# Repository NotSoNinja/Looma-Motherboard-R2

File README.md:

Looma-Motherboard-R2
====================

Revision 2+ of Looma's Motherboard

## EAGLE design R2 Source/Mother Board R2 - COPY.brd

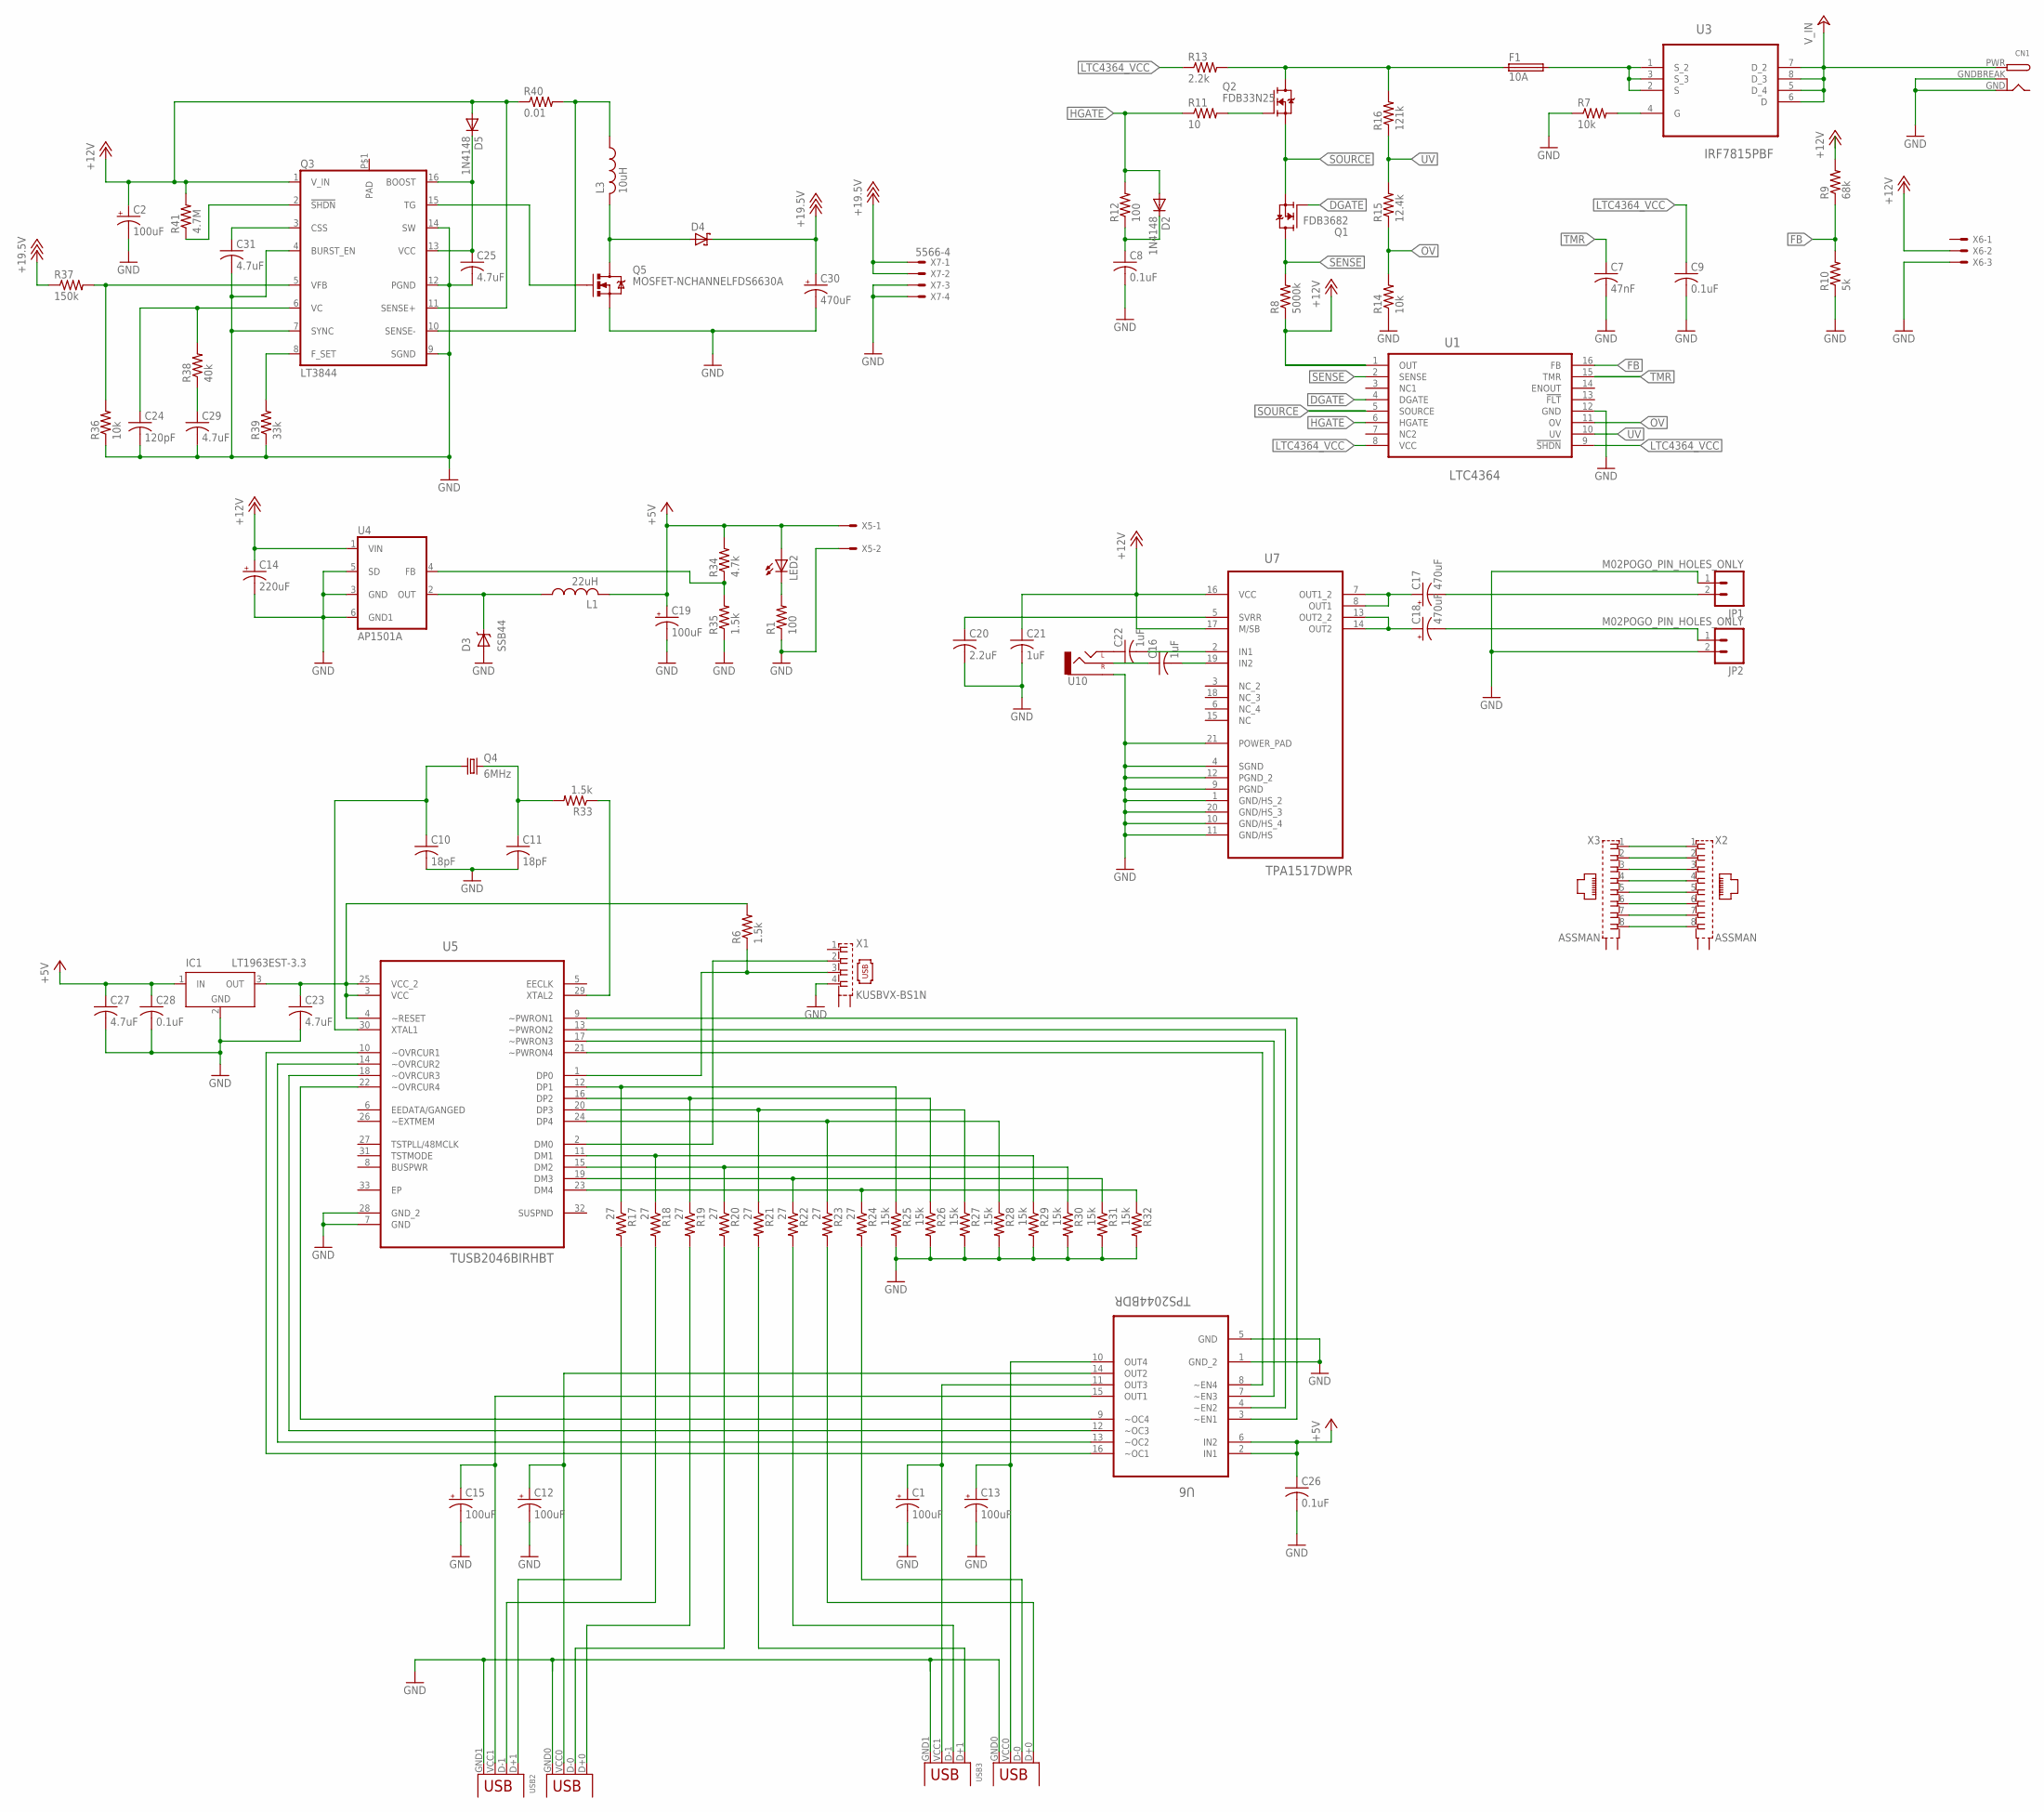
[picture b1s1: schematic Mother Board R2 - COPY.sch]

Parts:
C1, C2, C12, C13, C15, C19: 100uF; PANASONIC_D; MPN 107SML016M
C7: 47nF; C1206; MPN 12061C473KAZ1A
C8, C9, C26, C28: 0.1uF; C0603; MPN 0603YC104MAT2A
C10, C11: 18pF; C0603; MPN 06035A180JAT2A
C14: 220uF; PANASONIC_D; MPN 16SVPF270M
C16, C21, C22: 1uF; C1206; MPN C1206C105K3RACTU
C17, C18, C30: 470uF; PANASONIC_D; MPN 107SML016M
C20: 2.2uF; C1206; MPN 1206YC225KAT2A
C23, C25, C27, C29, C31: 4.7uF; C0805; MPN CGA4J3X7R1C475K125AB
C24: 120pF; C0805; MPN CGA4J3X7R1C475K125AB
CN1: DCBARRELPTH; DCJACK_2MM_PTH
D2, D5: 1N4148; SOD323; MPN 1N4148WS-7-F
D3: SSB44; SMB; MPN SSB44-E3/52T
D4: SCHOTTKY-DIODESMC; DIODE_SMC; MPN B550C-13-F
F1: 10A; MINIFUSE; MPN 01530007Z
IC1: LT1963EST-3.3; SOT223
JP1, JP2: M02POGO_PIN_HOLES_ONLY; 1X02_PP_HOLES_ONLY
L1: 22uH; BOURNSIND; MPN SRR1280-220M
L3: 10uH; BOURNSIND; MPN SRR1280-220M
LED2: LEDCHIPLED_1206; CHIPLED_1206; MPN KP-3216CGCK
Q1: FDB3682; TO263; MPN STB35NF10T4
Q2: FDB33N25; TO263; MPN FDB33N25TM
Q3: LT3844; TSSOP16-TPAD
Q4: 6MHz; HC49UP; MPN ABLSG-6.000MHZ-D-2-Y-T
Q5: MOSFET-NCHANNELFDS6630A; SO08
R1, R12: 100; R1206; MPN MCHP06W2F1000T5E
R6, R33: 1.5k; R1206; MPN MCHP06W2F1501T5E
R7, R14, R36: 10k; R1206; MPN MCHP06W2F1002T5E
R8: 5000k; R1206; MPN CRCW12065M10JNEA
R9: 68k; R1206; MPN CRCW120668K0FKEA
R10: 5k; R1206; MPN ERJ-8ENF5101V
R11: 10; R1206; MPN CRM1206-FX-10R0ELF
R13: 2.2k; R1206; MPN CRCW12062K20FKTA
R15: 12.4k; R1206; MPN CRCW120612K4FKEA
R16: 121k; R1206; MPN CRCW1206121KFKEA
R17, R18, R19, R20, R21, R22, R23, R24: 27; R1206; MPN MCHP06W2F270JT5E
R25, R26, R27, R28, R29, R30, R31, R32: 15k; R1206; MPN MCHP06W2F1502T5E
R34: 4.7k; R1206; MPN MC0125W12061120K
R35: 1.5k; R1206; MPN MC0125W12061120K
R37: 150k; R1206; MPN MCHP06W2F1002T5E
R38: 40k; R1206; MPN MCHP06W2F1002T5E
R39: 33k; R1206; MPN MCHP06W2F1002T5E
R40: 0.01; R1206; MPN MCHP06W2F1002T5E
R41: 4.7M; R1206; MPN MCHP06W2F1002T5E
U1: LTC4364; MSOP-16; MPN LTC4364IS-1#PBF
U3: IRF7815PBF; SOIC127P600X175-8N
U4: AP1501A; TO263-5
U5: TUSB2046BIRHBT; QFN50P500X500X100-33N
U6: TPS2044BDR; SOIC127P600X175-16N
U7: TPA1517DWPR; SOIC127P1030X265-21N; MPN TPA1517DWPR
U10: AUDIO-JACKPTH; AUDIO-JACK; MPN SPC21348
USB2, USB3: DUALUSB; USB-A-DS; MPN 5787617-1
X1: KUSBVX-BS1N; MPN MC32597
X2, X3: ASSMAN
X5: KK-156-2
X6: KK-156-3
X7: 5566-4; MPN 39-29-9042

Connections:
+5V: C19.+, C26.1, C27.1, C28.1, IC1.1 (IN), L1.P$2 (2), LED2.A, R34.2, U6.2 (IN1), U6.6 (IN2), X5.1
+12V: C2.+, C14.+, C21.1, D5.A, Q3.1 (V_IN), Q3.11 (SENSE+), R8.1, R9.2, R40.1, R41.2, U1.1 (OUT), U4.1 (VIN), U7.16 (VCC), U7.17 (M/SB), X6.2
+18V: C30.+, D4.C (A), R37.1, X7.1, X7.2
DGATE: Q1.1 (G), U1.4 (DGATE)
FB: R9.1, R10.2, U1.16 (FB)
GND: C1.-, C2.-, C7.2, C8.2, C9.2, C10.2, C11.2, C12.-, C13.-, C14.-, C15.-, C19.-, C20.2, C21.2, C23.2, C24.2, C25.2, C26.2, C27.2, C28.2, C29.2, C30.-, C31.2, CN1.GND, CN1.GNDBREAK, D3.A, IC1.2 (GND), IC1.4 (GND), JP1.1, JP2.2, Q3.4 (BURST_EN), Q3.7 (SYNC), Q3.9 (SGND), Q3.12 (PGND), Q3.14 (SW), Q5.1 (S), Q5.2 (S), Q5.3 (S), R1.1, R7.1, R10.1, R14.1, R25.2, R26.2, R27.2, R28.2, R29.2, R30.2, R31.2, R32.2, R35.1, R36.1, R39.1, U1.12 (GND), U4.3 (GND), U4.5 (SD), U4.6 (GND1), U5.7 (GND), U5.28 (GND_2), U6.1 (GND_2), U6.5 (GND), U7.1 (GND/HS_2), U7.4 (SGND), U7.9 (PGND), U7.10 (GND/HS_4), U7.11 (GND/HS), U7.12 (PGND_2), U7.20 (GND/HS_3), U7.21 (POWER_PAD), U10.SLEEVE, USB2.GND0 (GND), USB2.GND1, USB3.GND0 (GND), USB3.GND1, X1.4, X5.2, X6.3, X7.3, X7.4
HGATE: D2.A, R11.1, R12.2, U1.6 (HGATE)
LTC4364_VCC: C9.1, R13.1, U1.8 (VCC), U1.9 (!SHDN)
unnamed: F1.P$1 (1), Q2.3 (D), R13.2, R16.2
unnamed: D3.C, L1.P$1 (1), U4.2 (OUT)
unnamed: LED2.C, R1.2
unnamed: U5.2 (DM0), X1.2
unnamed: R6.1, U5.1 (DP0), X1.3
unnamed: C23.1, IC1.3 (OUT), R6.2, U5.3 (VCC), U5.4 (~RESET), U5.25 (VCC_2)
unnamed: R17.1, R25.1, U5.12 (DP1)
unnamed: Q2.1 (G), R11.2
unnamed: R18.1, R29.1, U5.11 (DM1)
unnamed: C8.1, D2.C, R12.1
unnamed: R19.1, R26.1, U5.16 (DP2)
unnamed: F1.P$2 (2), U3.1 (S_2), U3.2 (S), U3.3 (S_3)
unnamed: R20.1, R30.1, U5.15 (DM2)
unnamed: R7.2, U3.4 (G)
unnamed: R21.1, R27.1, U5.20 (DP3)
unnamed: R22.1, R31.1, U5.19 (DM3)
unnamed: R23.1, R28.1, U5.24 (DP4)
unnamed: R24.1, R32.1, U5.23 (DM4)
unnamed: C10.1, Q4.1, U5.30 (XTAL1)
unnamed: C11.1, Q4.2, R33.2
unnamed: R33.1, U5.29 (XTAL2)
unnamed: U5.21 (~PWRON4), U6.8 (~EN4)
unnamed: U5.17 (~PWRON3), U6.7 (~EN3)
unnamed: U5.13 (~PWRON2), U6.4 (~EN2)
unnamed: U5.9 (~PWRON1), U6.3 (~EN1)
unnamed: U5.22 (~OVRCUR4), U6.9 (~OC4)
unnamed: U5.18 (~OVRCUR3), U6.12 (~OC3)
unnamed: U5.14 (~OVRCUR2), U6.13 (~OC2)
unnamed: U5.10 (~OVRCUR1), U6.16 (~OC1)
unnamed: C15.+, U6.15 (OUT1), USB2.VCC1 (VBUS1)
unnamed: C12.+, U6.14 (OUT2), USB2.VCC0 (VBUS)
unnamed: C1.+, U6.11 (OUT3), USB3.VCC1 (VBUS1)
unnamed: C13.+, U6.10 (OUT4), USB3.VCC0 (VBUS)
unnamed: R17.2, USB2.D+1
unnamed: R18.2, USB2.D-1
unnamed: R19.2, USB2.D+0 (D+)
unnamed: R20.2, USB2.D-0 (D-)
unnamed: R21.2, USB3.D+1
unnamed: R22.2, USB3.D-1
unnamed: R23.2, USB3.D+0 (D+)
unnamed: R24.2, USB3.D-0 (D-)
unnamed: C20.1, U7.5 (SVRR)
unnamed: C22.1, U10.TIP (LEFT)
unnamed: C22.2, U7.2 (IN1)
unnamed: C16.1, U10.RING (RIGHT)
unnamed: C16.2, U7.19 (IN2)
unnamed: C17.+, U7.7 (OUT1_2), U7.8 (OUT1)
unnamed: C18.+, U7.13 (OUT2_2), U7.14 (OUT2)
unnamed: C18.-, JP2.1
unnamed: C17.-, JP1.2
unnamed: X2.1, X3.1
unnamed: X2.2, X3.2
unnamed: X2.3, X3.3
unnamed: X2.4, X3.4
unnamed: X2.5, X3.5
unnamed: X2.6, X3.6
unnamed: X2.7, X3.7
unnamed: X2.8, X3.8
unnamed: R34.1, R35.2, U4.4 (FB)
unnamed: Q3.2 (!SHDN), R41.1
unnamed: C31.1, Q3.3 (CSS)
unnamed: C24.1, Q3.6 (VC), R38.2
unnamed: C29.1, R38.1
unnamed: Q3.5 (VFB), R36.2, R37.2
unnamed: Q3.8 (F_SET), R39.2
unnamed: C25.1, D5.C, Q3.13 (VCC), Q3.16 (BOOST)
unnamed: L3.P$1 (1), Q3.10 (SENSE-), R40.2
unnamed: Q3.15 (TG), Q5.4 (G)
unnamed: D4.A (C), L3.P$2 (2), Q5.5 (D), Q5.6 (D), Q5.7 (D), Q5.8 (D)
OV: R14.2, R15.1, U1.11 (OV)
SENSE: Q1.3 (D), R8.2, U1.2 (SENSE)
SOURCE: Q1.2 (S), Q2.2 (S), U1.5 (SOURCE)
TMR: C7.1, U1.15 (TMR)
UV: R15.2, R16.1, U1.10 (UV)
V_IN: CN1.PWR, U3.5 (D_4), U3.6 (D), U3.7 (D_2), U3.8 (D_3)

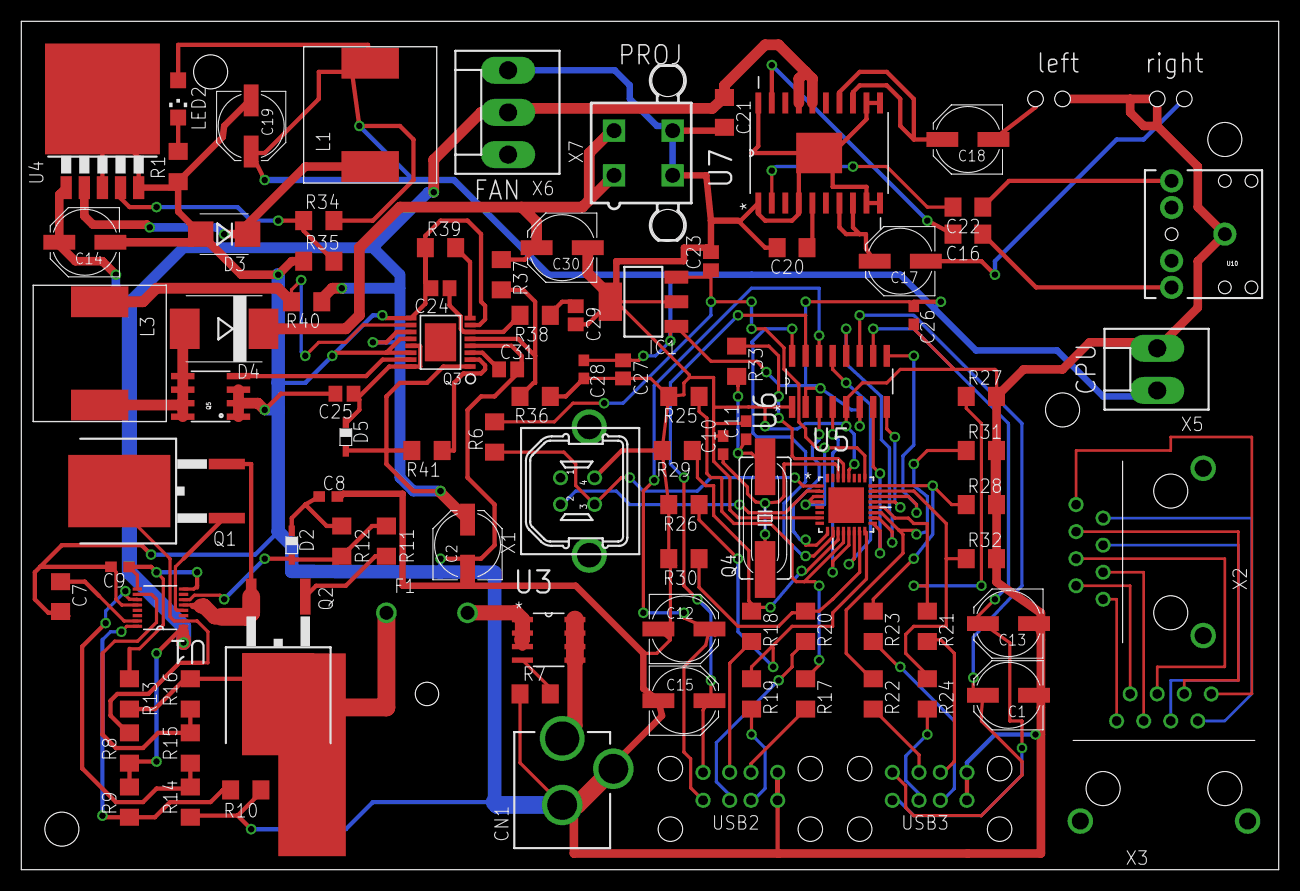
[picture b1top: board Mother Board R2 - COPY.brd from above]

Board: 2 copper layers, 118.1 x 79.7 mm, 96 parts (0 on the bottom side), 83 nets.

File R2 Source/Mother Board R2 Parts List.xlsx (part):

Part | Value | Device | Package | Description | MF | MPN | OC_FARNELL | OC_NEWARK | PACKAGE | PROD_ID | SPICEMODEL | SPICEPREFIX | SPICETYPE | SUPPLIER
R40 | 0.01 | R-US_R1206 | R1206 | RESISTOR, American symbol |  | MCHP06W2F1002T5E |  | 01N7135
R11 | 10 | R-US_R1206 | R1206 | RESISTOR, American symbol |  | CRM1206-FX-10R0ELF |  | 17T4257
R17 | 27 | R-US_R1206 | R1206 | RESISTOR, American symbol |  | MCHP06W2F270JT5E |  | 01N7163
R18 | 27 | R-US_R1206 | R1206 | RESISTOR, American symbol |  | MCHP06W2F270JT5E |  | 01N7163
R19 | 27 | R-US_R1206 | R1206 | RESISTOR, American symbol |  | MCHP06W2F270JT5E |  | 01N7163
R20 | 27 | R-US_R1206 | R1206 | RESISTOR, American symbol |  | MCHP06W2F270JT5E |  | 01N7163
R21 | 27 | R-US_R1206 | R1206 | RESISTOR, American symbol |  | MCHP06W2F270JT5E |  | 01N7163
R22 | 27 | R-US_R1206 | R1206 | RESISTOR, American symbol |  | MCHP06W2F270JT5E |  | 01N7163
R23 | 27 | R-US_R1206 | R1206 | RESISTOR, American symbol |  | MCHP06W2F270JT5E |  | 01N7163
R24 | 27 | R-US_R1206 | R1206 | RESISTOR, American symbol |  | MCHP06W2F270JT5E |  | 01N7163
R1 | 100 | R-US_R1206 | R1206 | RESISTOR, American symbol |  | MCHP06W2F1000T5E |  | 01N7133
R12 | 100 | R-US_R1206 | R1206 | RESISTOR, American symbol |  | MCHP06W2F1000T5E |  | 01N7133
C8 | 0.1uF | C-USC0603 | C0603 | CAPACITOR, American symbol |  | 0603YC104MAT2A |  | 96M1177
C9 | 0.1uF | C-USC0603 | C0603 | CAPACITOR, American symbol |  | 0603YC104MAT2A |  | 96M1177
C26 | 0.1uF | C-USC0603 | C0603 | CAPACITOR, American symbol |  | 0603YC104MAT2A |  | 96M1177
C28 | 0.1uF | C-USC0603 | C0603 | CAPACITOR, American symbol |  | 0603YC104MAT2A |  | 96M1177
R6 | 1.5k | R-US_R1206 | R1206 | RESISTOR, American symbol |  | MCHP06W2F1501T5E |  | 01N7147
R33 | 1.5k | R-US_R1206 | R1206 | RESISTOR, American symbol |  | MCHP06W2F1501T5E |  | 01N7147
R35 | 1.5k | R-US_R1206 | R1206 | RESISTOR, American symbol |  | MCHP06W2F1501T5E |  | 01N7147
C1 | 100uF | CPOL-USD | PANASONIC_D | POLARIZED CAPACITOR, American symbol |  | 107SML016M |  | 99M1145
C2 | 100uF | CPOL-USD | PANASONIC_D | POLARIZED CAPACITOR, American symbol |  | 107SML016M |  | 99M1145
C12 | 100uF | CPOL-USD | PANASONIC_D | POLARIZED CAPACITOR, American symbol |  | 107SML016M |  | 99M1145
C13 | 100uF | CPOL-USD | PANASONIC_D | POLARIZED CAPACITOR, American symbol |  | 107SML016M |  | 99M1145
C15 | 100uF | CPOL-USD | PANASONIC_D | POLARIZED CAPACITOR, American symbol |  | 107SML016M |  | 99M1145
C19 | 100uF | CPOL-USD | PANASONIC_D | POLARIZED CAPACITOR, American symbol |  | 107SML016M |  | 99M1145
F1 | 10A | MINIFUSE | MINIFUSE |  | LITTELFUSE | 01530007Z |  | 67K1420
R7 | 10k | R-US_R1206 | R1206 | RESISTOR, American symbol |  | MCHP06W2F1002T5E |  | 01N7135
R14 | 10k | R-US_R1206 | R1206 | RESISTOR, American symbol |  | MCHP06W2F1002T5E |  | 01N7135
R36 | 10k | R-US_R1206 | R1206 | RESISTOR, American symbol |  | MCHP06W2F1002T5E |  | 01N7135
L3 | 10uH | L-US | BOURNSIND | INDUCTOR, American symbol |  | SRR1280-220M |  | 07W8494
R15 | 12k | R-US_R1206 | R1206 | RESISTOR, American symbol | VISHAY/DALE | CRCW120612K4FKEA |  | 53K1950
C24 | 120pF | C-USC0805 | C0805 | CAPACITOR, American symbol |  | CGA4J3X7R1C475K125AB |  | 04X3165
R16 | 121k | R-US_R1206 | R1206 | RESISTOR, American symbol | VISHAY/DALE | CRCW1206121KFKEA |  | 53K1959
R37 | 150k | R-US_R1206 | R1206 | RESISTOR, American symbol |  | MCHP06W2F1002T5E |  | 01N7135
R25 | 15k | R-US_R1206 | R1206 | RESISTOR, American symbol |  | MCHP06W2F1502T5E |  | 01N7148
R26 | 15k | R-US_R1206 | R1206 | RESISTOR, American symbol |  | MCHP06W2F1502T5E |  | 01N7148
R27 | 15k | R-US_R1206 | R1206 | RESISTOR, American symbol |  | MCHP06W2F1502T5E |  | 01N7148
R28 | 15k | R-US_R1206 | R1206 | RESISTOR, American symbol |  | MCHP06W2F1502T5E |  | 01N7148
R29 | 15k | R-US_R1206 | R1206 | RESISTOR, American symbol |  | MCHP06W2F1502T5E |  | 01N7148
R30 | 15k | R-US_R1206 | R1206 | RESISTOR, American symbol |  | MCHP06W2F1502T5E |  | 01N7148
R31 | 15k | R-US_R1206 | R1206 | RESISTOR, American symbol |  | MCHP06W2F1502T5E |  | 01N7148
R32 | 15k | R-US_R1206 | R1206 | RESISTOR, American symbol |  | MCHP06W2F1502T5E |  | 01N7148
C10 | 18pF | C-USC0603 | C0603 | CAPACITOR, American symbol | AVX CORPORATION | 06035A180JAT2A |  | 17C6481
C11 | 18pF | C-USC0603 | C0603 | CAPACITOR, American symbol | AVX CORPORATION | 06035A180JAT2A |  | 17C6481
D2 | 1N4148 | 1N4148 | SOD323 |  |  | 1N4148WS-7-F |  | 12T2305
D5 | 1N4148 | 1N4148 | SOD323 |  |  | 1N4148WS-7-F |  | 12T2305
C21 | 1uF | C-USC1206 | C1206 | CAPACITOR, American symbol |  | C1206C105K3RACTU |  | 03M7475
R13 | 2.2k | R-US_R1206 | R1206 | RESISTOR, American symbol | VISHAY/DALE | CRCW12062K20FKTA |  | 07J5728
C20 | 2.2uF | C-USC1206 | C1206 | CAPACITOR, American symbol |  | 1206YC225KAT2A |  | 88W4192
C14 | 220uF | CPOL-USD | PANASONIC_D | POLARIZED CAPACITOR, American symbol |  | 16SVPF270M |  | 98W0218
L1 | 22uH | L-US | BOURNSIND | INDUCTOR, American symbol |  | SRR1280-220M |  | 07W8494
R39 | 33k | R-US_R1206 | R1206 | RESISTOR, American symbol |  | MCHP06W2F1002T5E |  | 01N7135
R34 | 4.7k | R-US_R1206 | R1206 | RESISTOR, American symbol |  | MCPWR06FTEO4701 |  | 43T5644
R41 | 4.7M | R-US_R1206 | R1206 | RESISTOR, American symbol |  | MCHP06W2F1002T5E |  | 01N7135
C16 | 4.7uF | C-USC1206 | C1206 | CAPACITOR, American symbol |  | C1206C105K3RACTU |  | 03M7475
C22 | 4.7uF | C-USC1206 | C1206 | CAPACITOR, American symbol |  | C1206C105K3RACTU |  | 03M7475
C23 | 4.7uF | C-USC0805 | C0805 | CAPACITOR, American symbol |  | CGA4J3X7R1C475K125AB |  | 04X3165
C25 | 4.7uF | C-USC0805 | C0805 | CAPACITOR, American symbol |  | CGA4J3X7R1C475K125AB |  | 04X3165
C27 | 4.7uF | C-USC0805 | C0805 | CAPACITOR, American symbol |  | CGA4J3X7R1C475K125AB |  | 04X3165
C29 | 4.7uF | C-USC0805 | C0805 | CAPACITOR, American symbol |  | CGA4J3X7R1C475K125AB |  | 04X3165
C31 | 4.7uF | C-USC0805 | C0805 | CAPACITOR, American symbol |  | CGA4J3X7R1C475K125AB |  | 04X3165
R38 | 39.2k | R-US_R1206 | R1206 | RESISTOR, American symbol |  | MCHP06W2F1002T5E |  | 01N7135
C17 | 470uF | CPOL-USD | PANASONIC_D | POLARIZED CAPACITOR, American symbol |  | 107SML016M |  | 99M1145
C18 | 470uF | CPOL-USD | PANASONIC_D | POLARIZED CAPACITOR, American symbol |  | 107SML016M |  | 99M1145
C30 | 470uF | CPOL-USD | PANASONIC_D | POLARIZED CAPACITOR, American symbol |  | 107SML016M |  | 99M1145
C7 | 47nF | C-USC1206 | C1206 | CAPACITOR, American symbol |  | 12061C473KAZ1A |  | 26M5748
R8 | 5.1M | R-US_R1206 | R1206 | RESISTOR, American symbol |  | CRCW12065M10JNEA |  | 59M6999
X7 | 5566-4 | 5566-4 | 5566-4 | Mini FIT connector 4 pol |  |  | unknown | unknown
R10 | 5.1k | R-US_R1206 | R1206 | RESISTOR, American symbol |  | ERJ-8ENF5101V |  | 53W4995
R9 | 68k | R-US_R1206 | R1206 | RESISTOR, American symbol | VISHAY/DALE | CRCW120668K0FKEA |  | 53K2569
Q4 | 6MHz | CRYSTALHC49UP | HC49UP | CRYSTAL |  | ABLSG-6.000MHZ-D-2-Y-T | unknown | 01T1342
U4 | AP1501A | AP1501A | TO263-5 |  |  |  |  | unknown
X2 | ASSMAN | ASSMAN | ASSMAN |  |  |  |  | unknown
X3 | ASSMAN | ASSMAN | ASSMAN |  |  |  |  | unknown
USB2 | DUALUSB | DUALUSB | USB-A-DS |  |  | 5787617-1 |  | 53K4503
USB3 | DUALUSB | DUALUSB | USB-A-DS |  |  | 5787617-1 |  | 53K4503
Q2 | FDB33N25 | FDB33N25 | TO263 |  |  | FDB33N25TM |  | 84W8845
Q1 | FDB3682 | FDB3682 | TO263 |  |  | STB35NF10T4 |  | 33R1119
U3 | IRF7240PBF | IRF7815PBF | SOIC127P600X175-8N | HEXFET Power MOSFET | INTERNATIONAL RECTIFIER(IR) | IRF7240PBF | 1865585 | 58K5775 | SOIC-8 |  |  |  |  | INTERNATIONAL RECTIFIER
X1 | KUSBVX-BS1N | KUSBVX-BS1N | KUSBVX-BS1N | USB B-type Receptacle Vertical, 4 Position, Through Hole |  | MC32597 |  | 46P5310
IC1 | LT1963EST-3.3 | LT1963EST-3.3 | SOT223 | 1.5A, Low Noise, Fast Transient Response LDO Regulator |  | LT1963EST-3.3 | 1501032 | 57M7546
Q3 | LT3844 | LT3844 | TSSOP16-TPAD |  |  | LT3844EFE |  | 57M8628
U1 | LTC4364 | LTC4364 | MSOP-16 | LTC4364 |  | LTC4364IS-1#PBF |  | 27W9491
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
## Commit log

2014-07-31 Updated License
    Changed to Attribution-Share-Alike-4.0-International
2014-07-31 CONTENT PATCH!
    Added WIP content for board
2014-07-31 Yay Defaults
    Added default git attributes file
2014-07-31 More Defaults
    Default gitignore added
2014-07-31 Added Original Source
    Colorado School of Mines board and schematic that continuing work is
    based on.
2014-07-31 Added Design Review Powerpoint
    Because reasons.
2014-08-07 Added folder for revision 2.5

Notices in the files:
parts and their libraries:
SparkFun-Connectors: Licensing: CC v3.0 Share-Alike You are welcome to use this library for commercial purposes.
